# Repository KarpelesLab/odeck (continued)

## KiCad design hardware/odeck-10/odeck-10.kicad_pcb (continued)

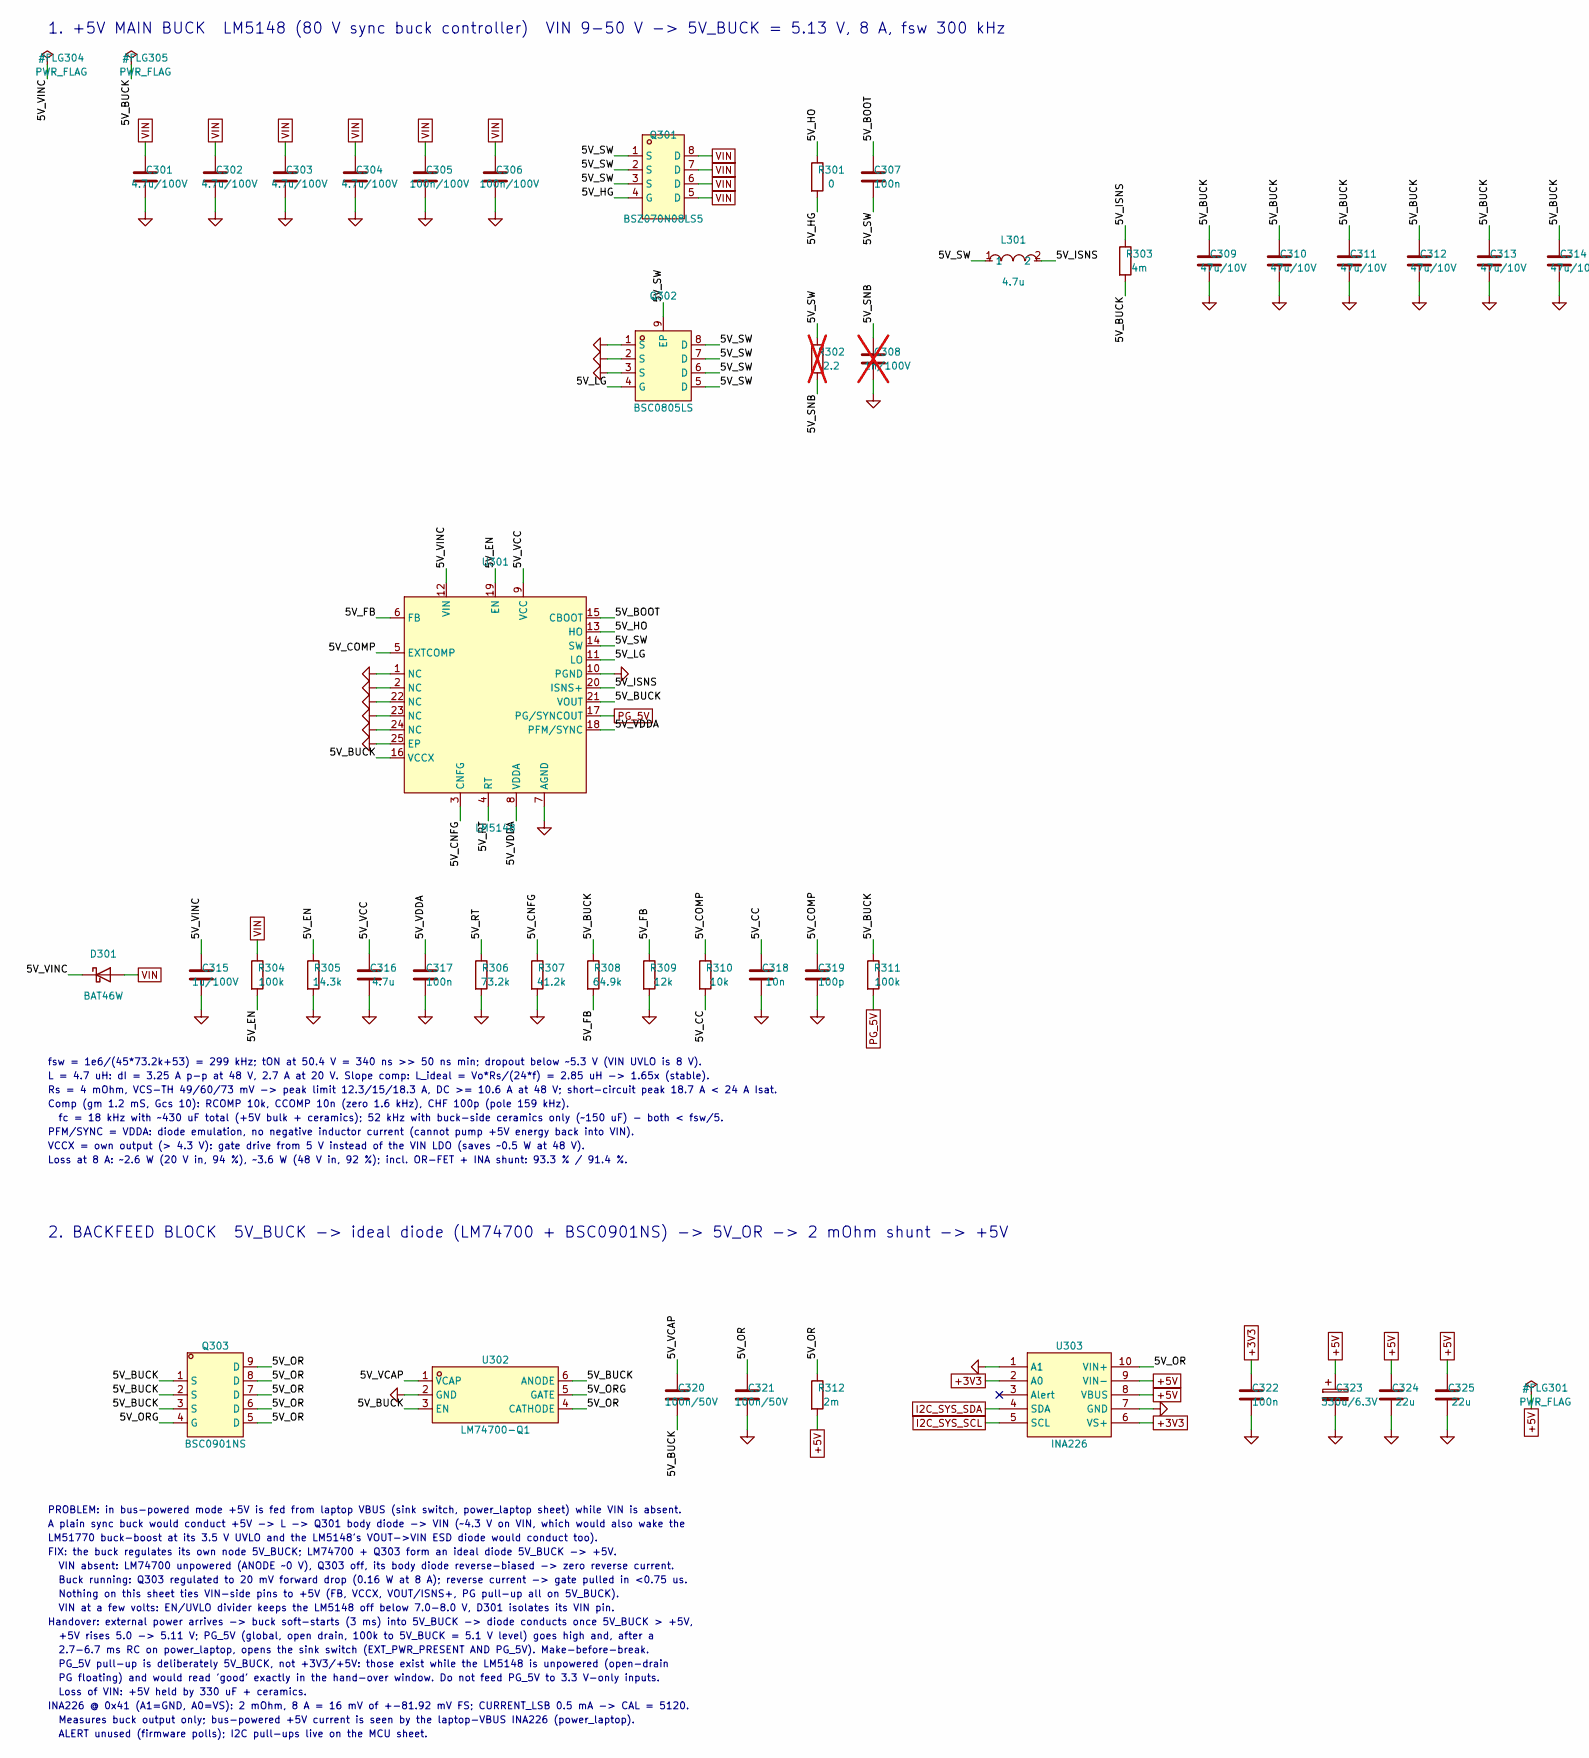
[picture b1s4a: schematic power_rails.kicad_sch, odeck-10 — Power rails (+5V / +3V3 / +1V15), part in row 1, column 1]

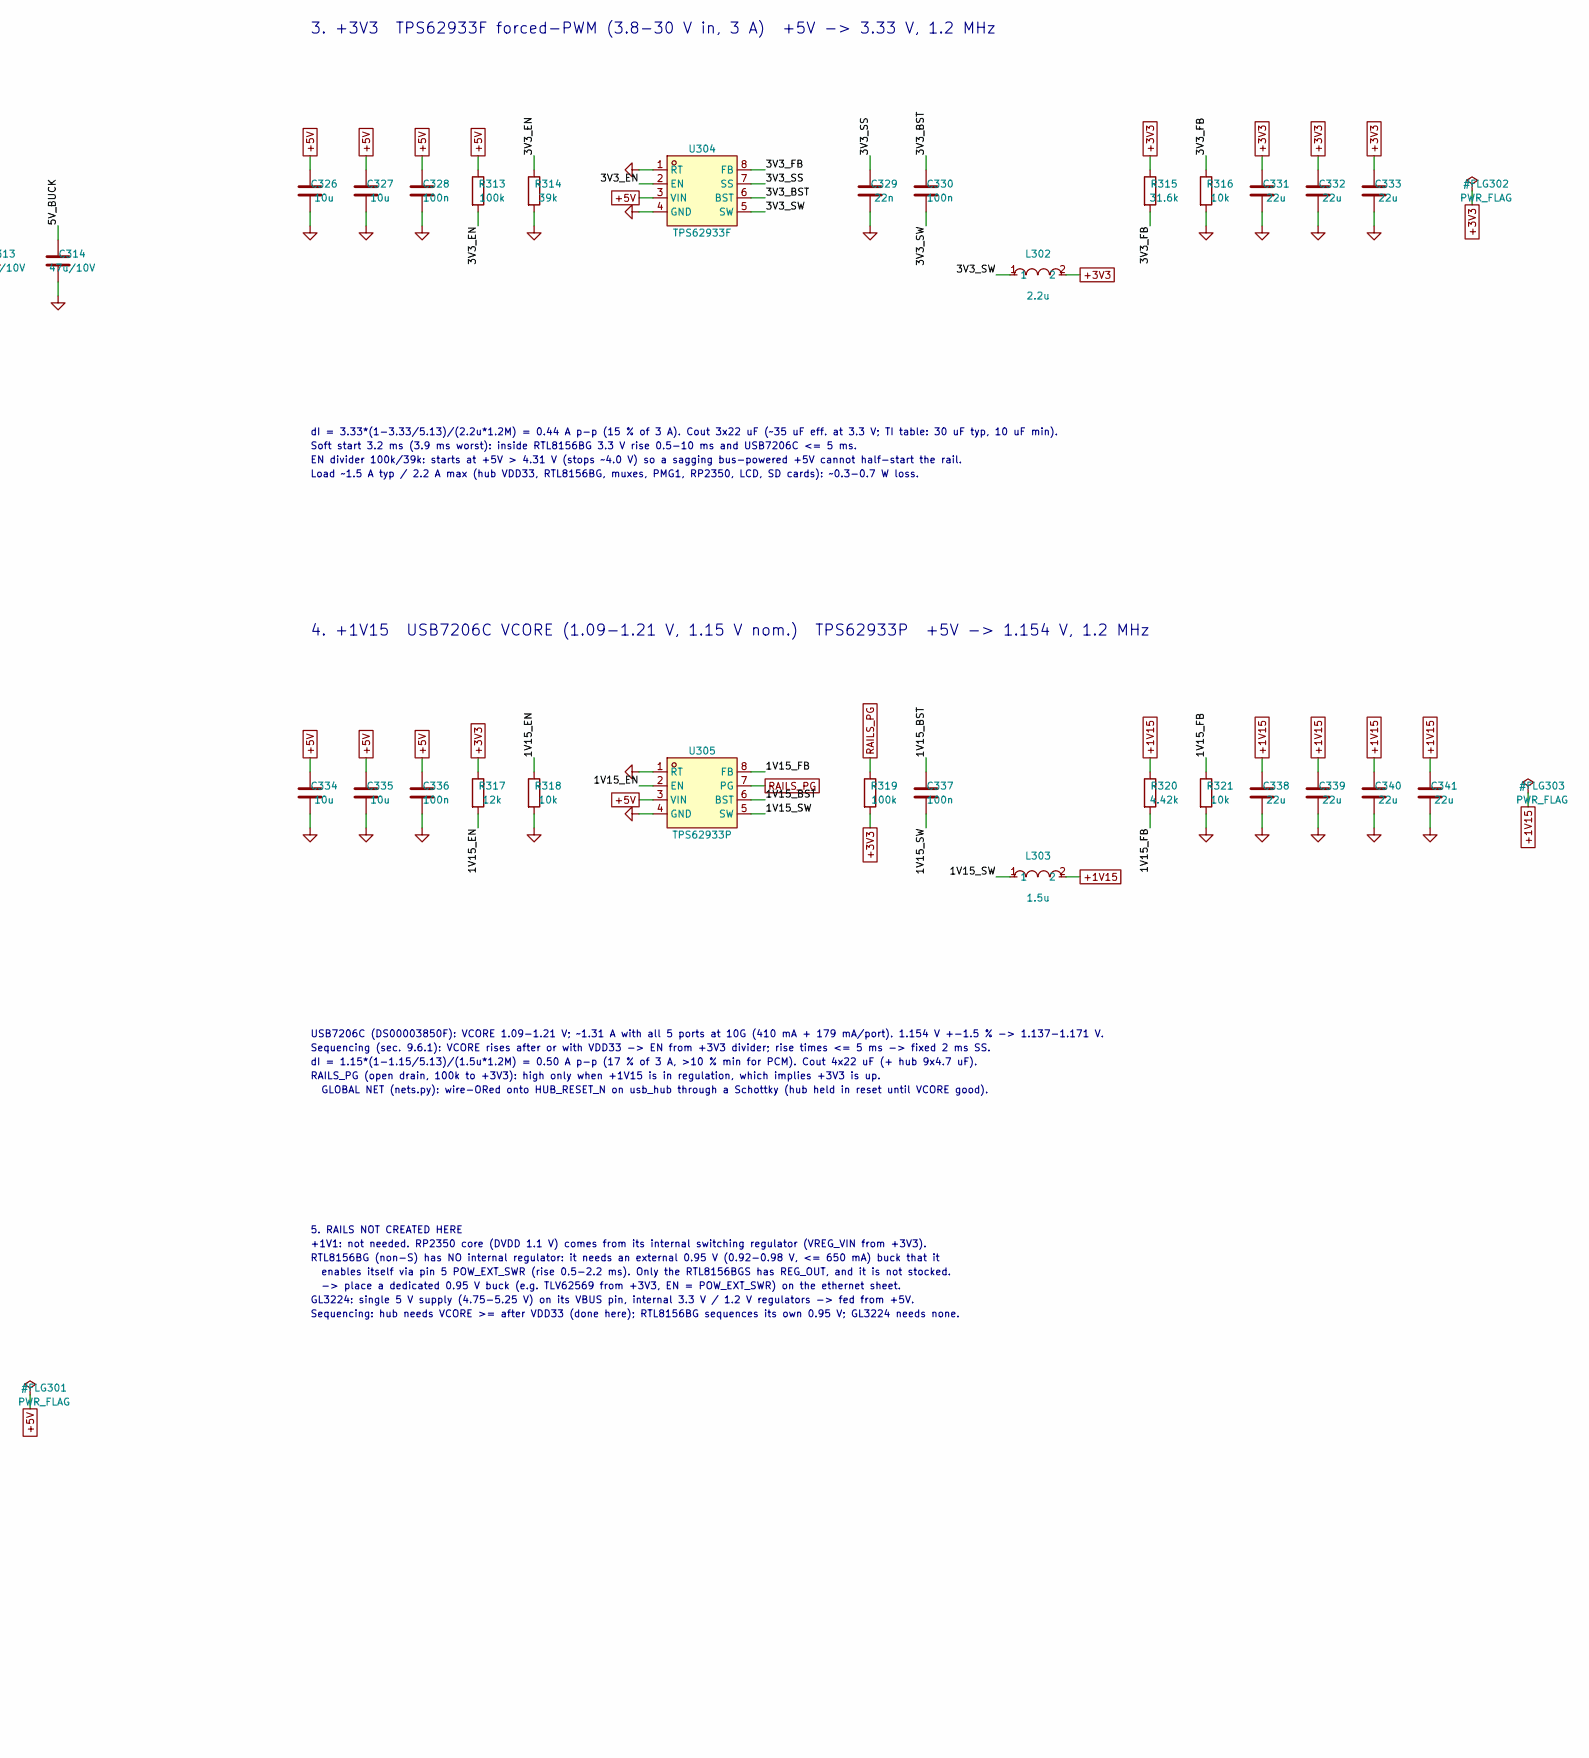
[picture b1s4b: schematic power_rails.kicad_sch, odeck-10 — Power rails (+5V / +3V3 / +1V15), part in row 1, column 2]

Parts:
C301, C302, C303, C304: 4.7u/100V; C_1210_3225Metric; LCSC C697607
C305, C306: 100n/100V; C_0805_2012Metric; LCSC C28233
C307, C317, C322, C328, C330, C336, C337: 100n; C_0402_1005Metric; LCSC C1525
C308: 1n/100V; C_0603_1608Metric; LCSC C106247; not fitted
C309, C310, C311, C312, C313, C314: 47u/10V; C_1210_3225Metric; LCSC C84494
C315: 1u/100V; C_0805_2012Metric; LCSC C126585
C316: 4.7u; C_0603_1608Metric; LCSC C19666
C318: 10n; C_0402_1005Metric; LCSC C15195
C319: 100p; C_0402_1005Metric; LCSC C1546
C320, C321: 100n/50V; C_0603_1608Metric; LCSC C14663
C323: 330u/6.3V; CP_Elec_6.3x5.9; LCSC C54321566
C324, C325, C331, C332, C333: 22u; C_0805_2012Metric; LCSC C45783
C326, C327, C334, C335: 10u; C_0805_2012Metric; LCSC C15850
C329: 22n; C_0402_1005Metric; LCSC C1532
C338, C339, C340, C341: 22u; C_0603_1608Metric; LCSC C59461
D301: BAT46W; D_SOD-123; LCSC C83152
L301: 4.7u; IND-SMD_L13.45-W12.6; MPN MWSA1206S-4R7MT; LCSC C408521
L302: 2.2u; IND-SMD_L5.4-W5.2; MPN MWSA0503S-2R2MT; LCSC C408408
L303: 1.5u; IND-SMD_L5.4-W5.2; MPN MWSA0503S-1R5MT; LCSC C408407
Q301: BSZ070N08LS5; PG-TSDSON-8_L3.3-W3.3-P0.65-BL-1; MPN BSZ070N08LS5; LCSC C534678
Q302: BSC0805LS; PG-TDSON-8_L5.2-W5.9-P1.27-LS6.2-BL-EP; MPN BSC0805LS; LCSC C534374
Q303: BSC0901NS; DFN-8_L5.9-W5.2-P1.27-LS6.2-BL; MPN BSC0901NS; LCSC C152424
R301: 0; R_0402_1005Metric; LCSC C17168
R302: 2.2; R_0805_2012Metric; LCSC C17521; not fitted
R303: 4m; R_2512_6332Metric; LCSC C459681
R304: 100k; R_0805_2012Metric; LCSC C149504
R305: 14.3k; R_0402_1005Metric; LCSC C25855
R306: 73.2k; R_0402_1005Metric; LCSC C26986
R307: 41.2k; R_0402_1005Metric; LCSC C100420
R308: 64.9k; R_0402_1005Metric; LCSC C26984
R309, R317: 12k; R_0402_1005Metric; LCSC C25752
R310, R316, R318, R321: 10k; R_0402_1005Metric; LCSC C25744
R311, R313, R319: 100k; R_0402_1005Metric; LCSC C25741
R312: 2m; R_2512_6332Metric; LCSC C459679
R314: 39k; R_0603_1608Metric; LCSC C23153
R315: 31.6k; R_0402_1005Metric; LCSC C11463
R320: 4.42k; R_0402_1005Metric; LCSC C52269
U301: LM5148; VQFN-24_L5.5-W3.5-P0.50-BL-EP-2; MPN LM5148RGYR; LCSC C7470701
U302: LM74700-Q1; SOT-23-6_L2.9-W1.6-P0.95-LS2.8-TL; MPN LM74700QDBVTQ1; LCSC C2653623
U303: INA226; MSOP-10_L3.0-W3.0-P0.50-LS5.0-BL; MPN INA226AIDGSR; LCSC C49851
U304: TPS62933F; SOT-583-8_L2.1-W1.2-P0.50-LS1.6-BR; MPN TPS62933FDRLR; LCSC C5219272
U305: TPS62933P; SOT-583-8_L2.1-W1.2-P0.50-LS1.6-BL; MPN TPS62933PDRLR; LCSC C5219254

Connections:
+1V15: C338.1, C339.1, C340.1, C341.1, L303.2, R320.1; also elsewhere on the board
+3V3: C322.1, C331.1, C332.1, C333.1, L302.2, R315.1, R317.1, R319.2, U303.2 (A0), U303.6 (VS+); also elsewhere on the board
+5V: C323.1, C324.1, C325.1, C326.1, C327.1, C328.1, C334.1, C335.1, C336.1, R312.2, R313.1, U303.8 (VBUS), U303.9 (VIN-), U304.3 (VIN), U305.3 (VIN); also elsewhere on the board
/Rails/1V15_BST: C337.1, U305.6 (BST)
/Rails/1V15_EN: R317.2, R318.1, U305.2 (EN)
/Rails/1V15_FB: R320.2, R321.1, U305.8 (FB)
/Rails/1V15_SW: C337.2, L303.1, U305.5 (SW)
/Rails/3V3_BST: C330.1, U304.6 (BST)
/Rails/3V3_EN: R313.2, R314.1, U304.2 (EN)
/Rails/3V3_FB: R315.2, R316.1, U304.8 (FB)
/Rails/3V3_SS: C329.1, U304.7 (SS)
/Rails/3V3_SW: C330.2, L302.1, U304.5 (SW)
/Rails/5V_BOOT: C307.1, U301.15 (CBOOT)
/Rails/5V_BUCK: C309.1, C310.1, C311.1, C312.1, C313.1, C314.1, C320.2, Q303.1 (S), Q303.2 (S), Q303.3 (S), R303.2, R308.1, R311.1, U301.16 (VCCX), U301.21 (VOUT), U302.3 (EN), U302.6 (ANODE)
/Rails/5V_CC: C318.1, R310.2
/Rails/5V_CNFG: R307.1, U301.3 (CNFG)
/Rails/5V_COMP: C319.1, R310.1, U301.5 (EXTCOMP)
/Rails/5V_EN: R304.2, R305.1, U301.19 (EN)
/Rails/5V_FB: R308.2, R309.1, U301.6 (FB)
/Rails/5V_HG: Q301.4 (G), R301.2
/Rails/5V_HO: R301.1, U301.13 (HO)
/Rails/5V_ISNS: L301.2, R303.1, U301.20 (ISNS+)
/Rails/5V_LG: Q302.4 (G), U301.11 (LO)
/Rails/5V_OR: C321.1, Q303.5 (D), Q303.6 (D), Q303.7 (D), Q303.8 (D), Q303.9 (D), R312.1, U302.4 (CATHODE), U303.10 (VIN+)
/Rails/5V_ORG: Q303.4 (G), U302.5 (GATE)
/Rails/5V_RT: R306.1, U301.4 (RT)
/Rails/5V_SNB: C308.1, R302.2
/Rails/5V_SW: C307.2, L301.1, Q301.1 (S), Q301.2 (S), Q301.3 (S), Q302.5 (D), Q302.6 (D), Q302.7 (D), Q302.8 (D), Q302.9 (EP), R302.1, U301.14 (SW)
/Rails/5V_VCAP: C320.1, U302.1 (VCAP)
/Rails/5V_VCC: C316.1, U301.9 (VCC)
/Rails/5V_VDDA: C317.1, U301.8 (VDDA), U301.18 (PFM/SYNC)
/Rails/5V_VINC: C315.1, D301.1 (K), U301.12 (VIN)
GND: C301.2, C302.2, C303.2, C304.2, C305.2, C306.2, C308.2, C309.2, C310.2, C311.2, C312.2, C313.2, C314.2, C315.2, C316.2, C317.2, C318.2, C319.2, C321.2, C322.2, C323.2, C324.2, C325.2, C326.2, C327.2, C328.2, C329.2, C331.2, C332.2, C333.2, C334.2, C335.2, C336.2, C338.2, C339.2, C340.2, C341.2, Q302.1 (S), Q302.2 (S), Q302.3 (S), R305.2, R306.2, R307.2, R309.2, R314.2, R316.2, R318.2, R321.2, U301.1 (NC), U301.2 (NC), U301.7 (AGND), U301.10 (PGND), U301.22 (NC), U301.23 (NC), U301.24 (NC), U301.25 (EP), U302.2 (GND), U303.1 (A1), U303.7 (GND), U304.1 (RT), U304.4 (GND), U305.1 (RT), U305.4 (GND); also elsewhere on the board
I2C_SYS_SCL: U303.5 (SCL); also elsewhere on the board
I2C_SYS_SDA: U303.4 (SDA); also elsewhere on the board
PG_5V: R311.2, U301.17 (PG/SYNCOUT); also elsewhere on the board
RAILS_PG: R319.1, U305.7 (PG); also elsewhere on the board
VIN: C301.1, C302.1, C303.1, C304.1, C305.1, C306.1, D301.2 (A), Q301.5 (D), Q301.6 (D), Q301.7 (D), Q301.8 (D), R304.1; also elsewhere on the board

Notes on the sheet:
1. +5V MAIN BUCK LM5148 (80 V sync buck controller) VIN 9-50 V -> 5V_BUCK = 5.13 V, 8 A, fsw 300 kHz
fsw = 1e6/(45*73.2k+53) = 299 kHz; tON at 50.4 V = 340 ns >> 50 ns min; dropout below ~5.3 V (VIN UVLO is 8 V).
L = 4.7 uH: dI = 3.25 A p-p at 48 V, 2.7 A at 20 V. Slope comp: L_ideal = Vo*Rs/(24*f) = 2.85 uH -> 1.65x (stable).
Rs = 4 mOhm, VCS-TH 49/60/73 mV -> peak limit 12.3/15/18.3 A, DC >= 10.6 A at 48 V; short-circuit peak 18.7 A < 24 A Isat.
Comp (gm 1.2 mS, Gcs 10): RCOMP 10k, CCOMP 10n (zero 1.6 kHz), CHF 100p (pole 159 kHz).
fc = 18 kHz with ~430 uF total (+5V bulk + ceramics); 52 kHz with buck-side ceramics only (~150 uF) - both < fsw/5.
PFM/SYNC = VDDA: diode emulation, no negative inductor current (cannot pump +5V energy back into VIN).
VCCX = own output (> 4.3 V): gate drive from 5 V instead of the VIN LDO (saves ~0.5 W at 48 V).
Loss at 8 A: ~2.6 W (20 V in, 94 %), ~3.6 W (48 V in, 92 %); incl. OR-FET + INA shunt: 93.3 % / 91.4 %.
2. BACKFEED BLOCK 5V_BUCK -> ideal diode (LM74700 + BSC0901NS) -> 5V_OR -> 2 mOhm shunt -> +5V
PROBLEM: in bus-powered mode +5V is fed from laptop VBUS (sink switch, power_laptop sheet) while VIN is absent.
A plain sync buck would conduct +5V -> L -> Q301 body diode -> VIN (~4.3 V on VIN, which would also wake the
LM51770 buck-boost at its 3.5 V UVLO and the LM5148's VOUT->VIN ESD diode would conduct too).
FIX: the buck regulates its own node 5V_BUCK; LM74700 + Q303 form an ideal diode 5V_BUCK -> +5V.
VIN absent: LM74700 unpowered (ANODE ~0 V), Q303 off, its body diode reverse-biased -> zero reverse current.
Buck running: Q303 regulated to 20 mV forward drop (0.16 W at 8 A); reverse current -> gate pulled in <0.75 us.
Nothing on this sheet ties VIN-side pins to +5V (FB, VCCX, VOUT/ISNS+, PG pull-up all on 5V_BUCK).
VIN at a few volts: EN/UVLO divider keeps the LM5148 off below 7.0-8.0 V, D301 isolates its VIN pin.
Handover: external power arrives -> buck soft-starts (3 ms) into 5V_BUCK -> diode conducts once 5V_BUCK > +5V,
+5V rises 5.0 -> 5.11 V; PG_5V (global, open drain, 100k to 5V_BUCK = 5.1 V level) goes high and, after a
2.7-6.7 ms RC on power_laptop, opens the sink switch (EXT_PWR_PRESENT AND PG_5V). Make-before-break.
PG_5V pull-up is deliberately 5V_BUCK, not +3V3/+5V: those exist while the LM5148 is unpowered (open-drain
PG floating) and would read 'good' exactly in the hand-over window. Do not feed PG_5V to 3.3 V-only inputs.
Loss of VIN: +5V held by 330 uF + ceramics.
INA226 @ 0x41 (A1=GND, A0=VS): 2 mOhm, 8 A = 16 mV of +-81.92 mV FS; CURRENT_LSB 0.5 mA -> CAL = 5120.
Measures buck output only; bus-powered +5V current is seen by the laptop-VBUS INA226 (power_laptop).
ALERT unused (firmware polls); I2C pull-ups live on the MCU sheet.
3. +3V3 TPS62933F forced-PWM (3.8-30 V in, 3 A) +5V -> 3.33 V, 1.2 MHz
dI = 3.33*(1-3.33/5.13)/(2.2u*1.2M) = 0.44 A p-p (15 % of 3 A). Cout 3x22 uF (~35 uF eff. at 3.3 V; TI table: 30 uF typ, 10 uF min).
Soft start 3.2 ms (3.9 ms worst): inside RTL8156BG 3.3 V rise 0.5-10 ms and USB7206C <= 5 ms.
EN divider 100k/39k: starts at +5V > 4.31 V (stops ~4.0 V) so a sagging bus-powered +5V cannot half-start the rail.
Load ~1.5 A typ / 2.2 A max (hub VDD33, RTL8156BG, muxes, PMG1, RP2350, LCD, SD cards): ~0.3-0.7 W loss.
4. +1V15 USB7206C VCORE (1.09-1.21 V, 1.15 V nom.) TPS62933P +5V -> 1.154 V, 1.2 MHz
USB7206C (DS00003850F): VCORE 1.09-1.21 V; ~1.31 A with all 5 ports at 10G (410 mA + 179 mA/port). 1.154 V +-1.5 % -> 1.137-1.171 V.
Sequencing (sec. 9.6.1): VCORE rises after or with VDD33 -> EN from +3V3 divider; rise times <= 5 ms -> fixed 2 ms SS.
dI = 1.15*(1-1.15/5.13)/(1.5u*1.2M) = 0.50 A p-p (17 % of 3 A, >10 % min for PCM). Cout 4x22 uF (+ hub 9x4.7 uF).
RAILS_PG (open drain, 100k to +3V3): high only when +1V15 is in regulation, which implies +3V3 is up.
GLOBAL NET (nets.py): wire-ORed onto HUB_RESET_N on usb_hub through a Schottky (hub held in reset until VCORE good).
5. RAILS NOT CREATED HERE
+1V1: not needed. RP2350 core (DVDD 1.1 V) comes from its internal switching regulator (VREG_VIN from +3V3).

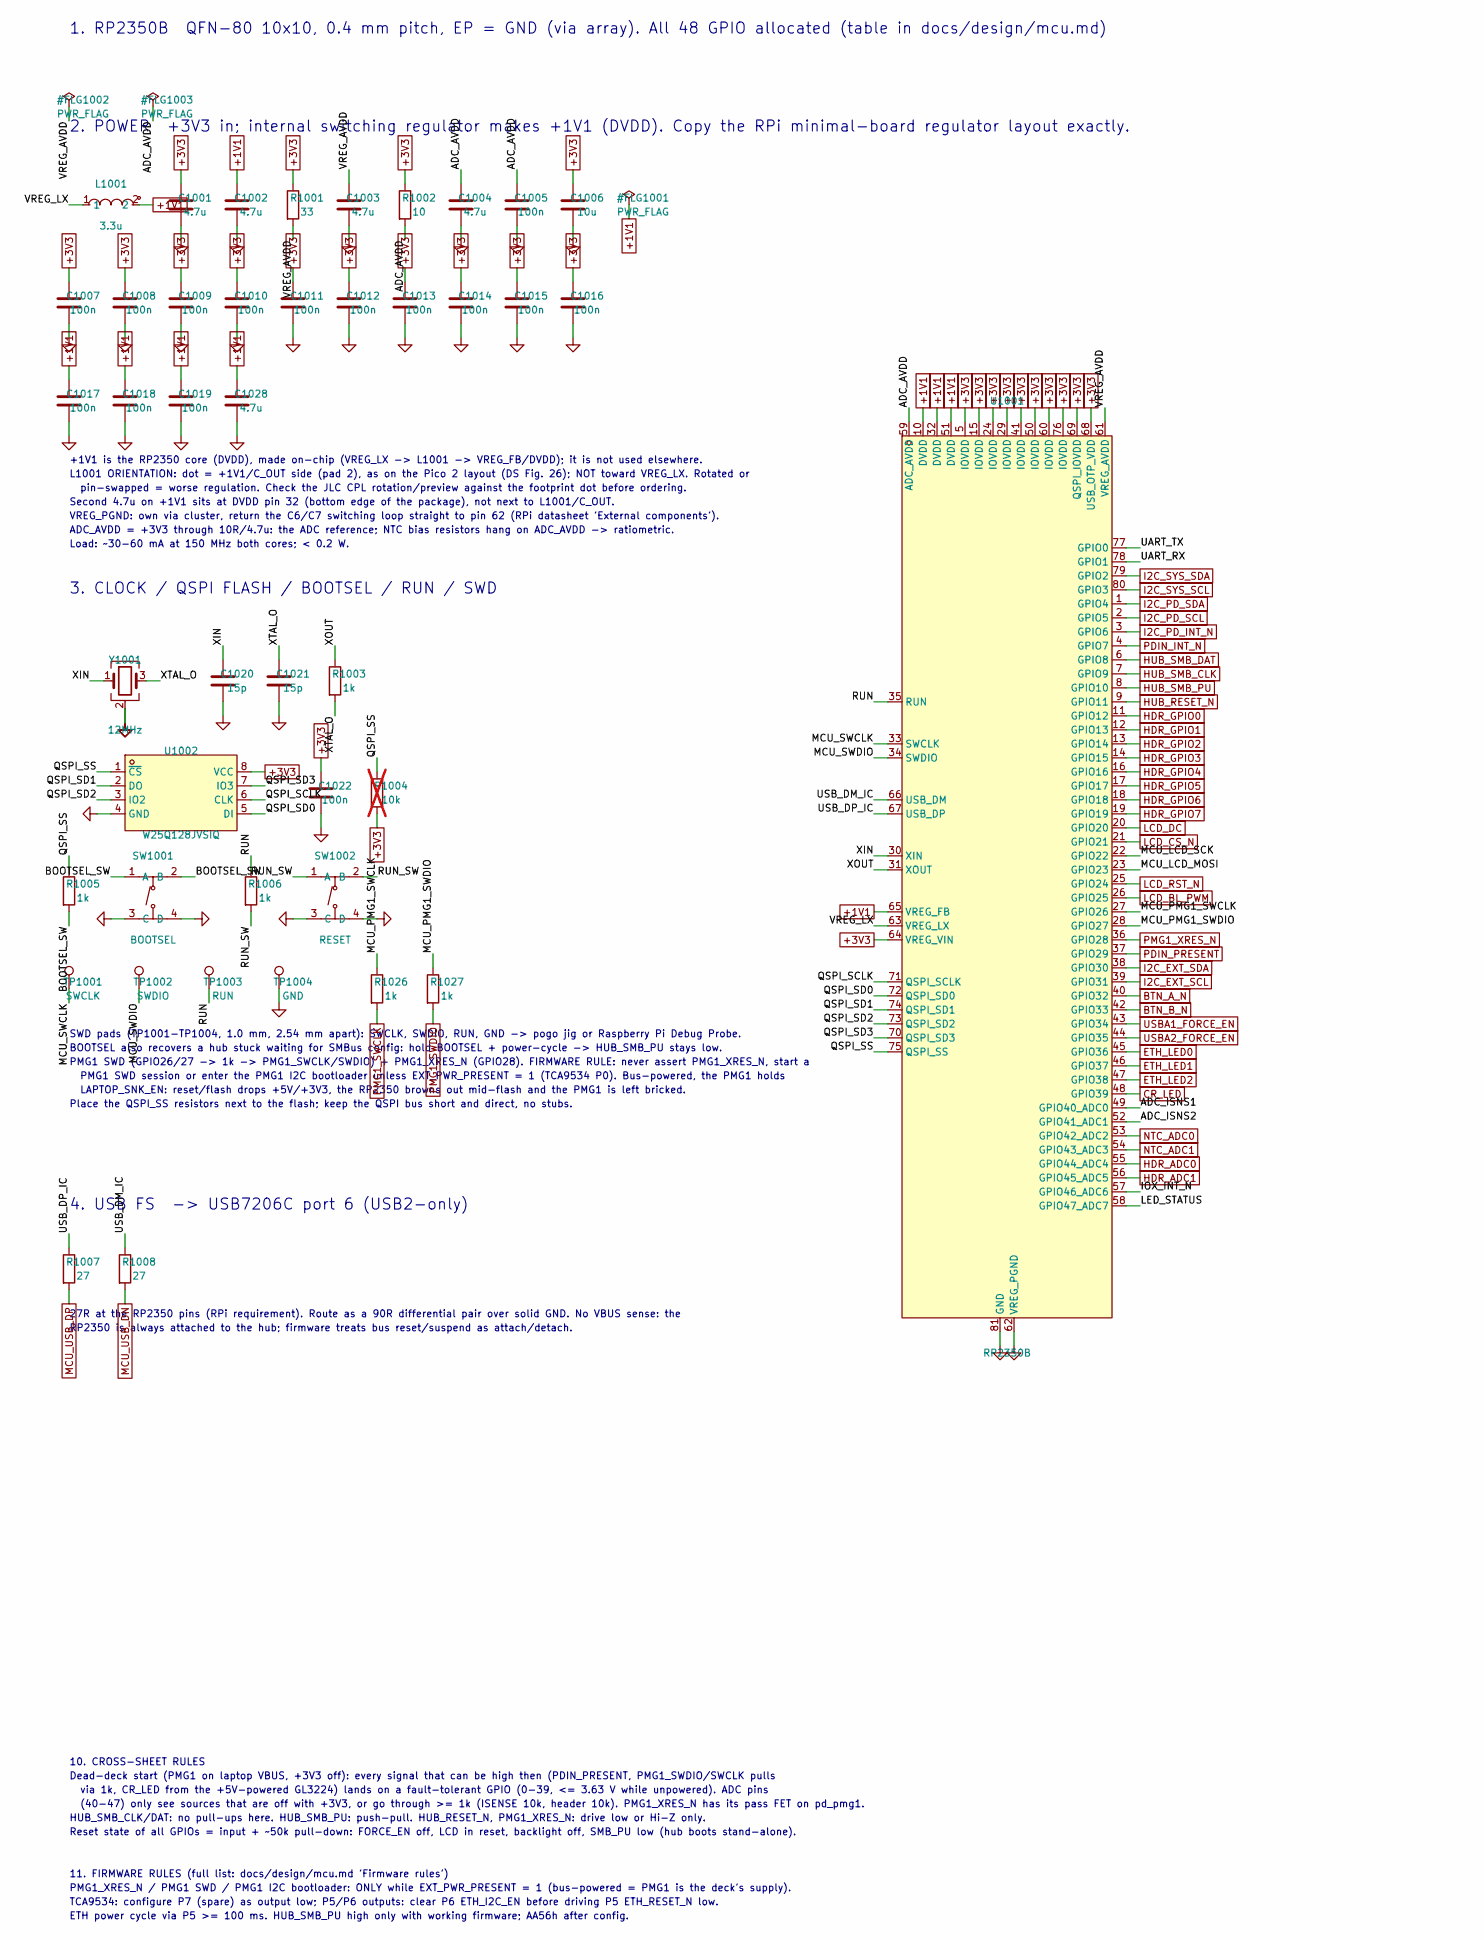
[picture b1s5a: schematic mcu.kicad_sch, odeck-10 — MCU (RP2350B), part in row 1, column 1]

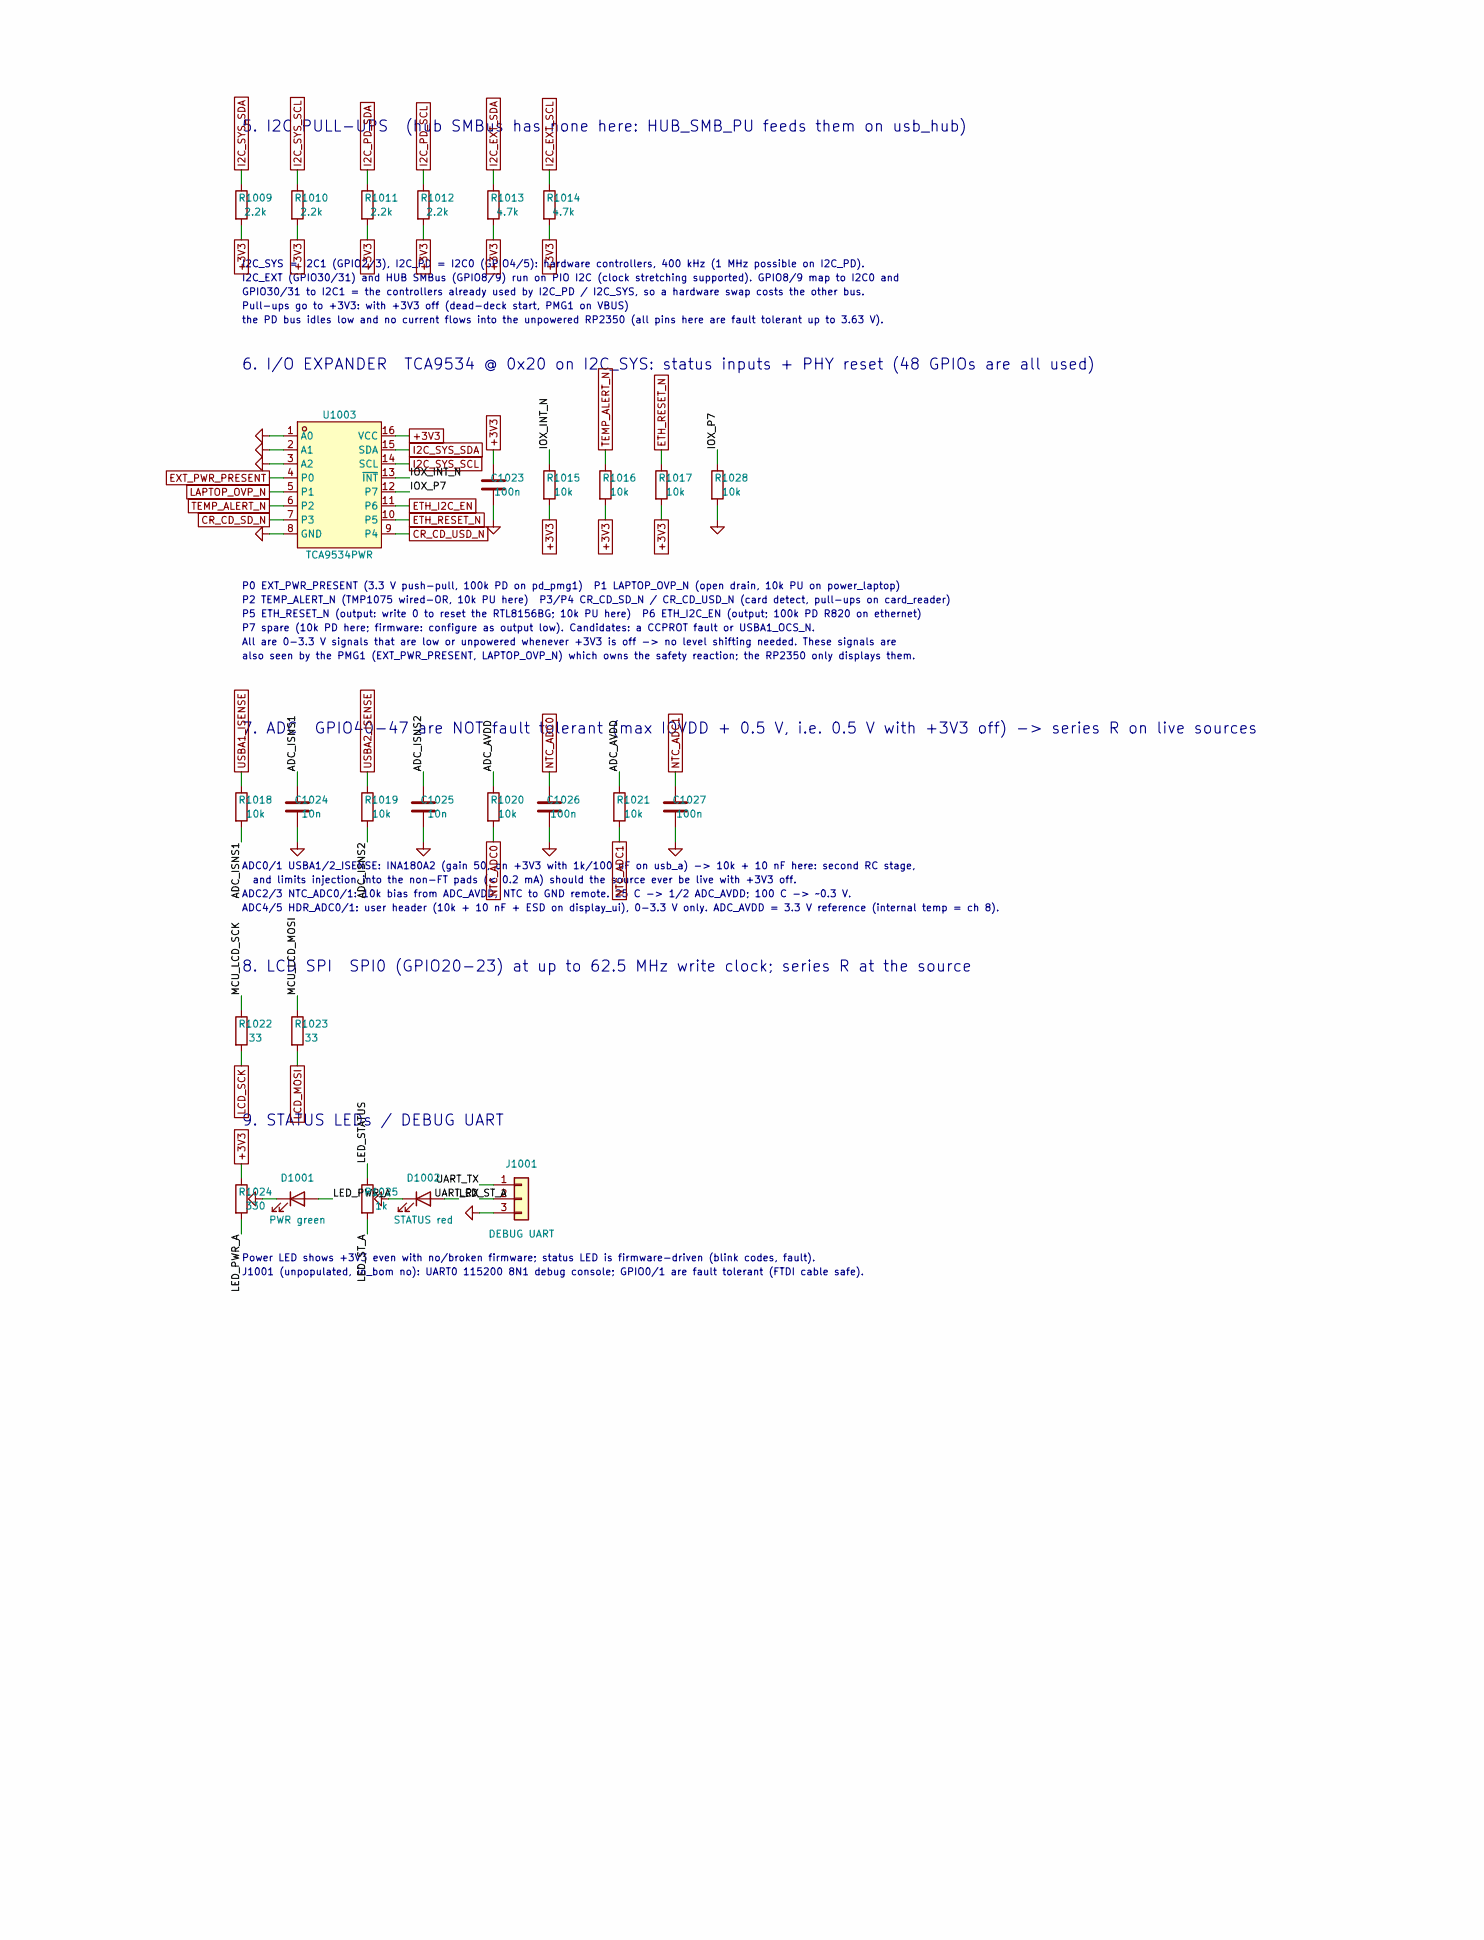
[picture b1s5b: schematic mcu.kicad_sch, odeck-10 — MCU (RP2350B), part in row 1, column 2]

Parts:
C1001, C1002, C1003, C1004, C1028: 4.7u; C_0402_1005Metric; LCSC C23733
C1005, C1007, C1008, C1009, C1010, C1011, C1012, C1013, C1014, C1015, C1016, C1017, C1018, C1019, C1022, C1023, C1026, C1027: 100n; C_0402_1005Metric; LCSC C1525
C1006: 10u; C_0603_1608Metric; LCSC C19702
C1020, C1021: 15p; C_0402_1005Metric; LCSC C1548
C1024, C1025: 10n; C_0402_1005Metric; LCSC C15195
D1001: PWR green; LED_0805_2012Metric; LCSC C2297
D1002: STATUS red; LED_0603_1608Metric; LCSC C2286
J1001: DEBUG UART; PinHeader_1x03_P2.54mm_Vertical
L1001: 3.3u; IND-SMD_L2.0-W1.6_AOTA-B201610S3R3-101-T; MPN AOTA-B201610S3R3-101-T; LCSC C42411119
R1001, R1022, R1023: 33; R_0402_1005Metric; LCSC C25105
R1002: 10; R_0402_1005Metric; LCSC C25077
R1003, R1005, R1006, R1025, R1026, R1027: 1k; R_0402_1005Metric; LCSC C11702
R1004: 10k; R_0402_1005Metric; LCSC C25744; not fitted
R1007, R1008: 27; R_0402_1005Metric; LCSC C25100
R1009, R1010, R1011, R1012: 2.2k; R_0402_1005Metric; LCSC C25879
R1013, R1014: 4.7k; R_0402_1005Metric; LCSC C25900
R1015, R1016, R1017, R1018, R1019, R1020, R1021, R1028: 10k; R_0402_1005Metric; LCSC C25744
R1024: 330; R_0402_1005Metric; LCSC C25104
SW1001: BOOTSEL; SW-SMD_4P-L5.1-W5.1-P3.70-LS6.5-TL_H1.5; MPN TS-1187A-B-A-B; LCSC C318884
SW1002: RESET; SW-SMD_4P-L5.1-W5.1-P3.70-LS6.5-TL_H1.5; MPN TS-1187A-B-A-B; LCSC C318884
TP1001: SWCLK; TestPoint_Pad_D1.0mm
TP1002: SWDIO; TestPoint_Pad_D1.0mm
TP1003: RUN; TestPoint_Pad_D1.0mm
TP1004: GND; TestPoint_Pad_D1.0mm
U1001: RP2350B; QFN-80_L10.0-W10.0-P0.40-TL-EP3.4; MPN RP2350B; LCSC C42415655
U1002: W25Q128JVSIQ; SOIC-8_L5.3-W5.3-P1.27-LS8.0-BL; MPN W25Q128JVSIQ; LCSC C97521
U1003: TCA9534PWR; TSSOP-16_L5.0-W4.4-P0.65-LS6.4-BL; MPN TCA9534PWR; LCSC C783615
Y1001: 12MHz; Crystal_SMD_3225-4Pin_3.2x2.5mm; LCSC C20625731

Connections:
+1V1: C1002.1, C1017.1, C1018.1, C1019.1, C1028.1, L1001.2, U1001.10 (DVDD), U1001.32 (DVDD), U1001.51 (DVDD), U1001.65 (VREG_FB)
+3V3: C1001.1, C1006.1, C1007.1, C1008.1, C1009.1, C1010.1, C1011.1, C1012.1, C1013.1, C1014.1, C1015.1, C1016.1, C1022.1, C1023.1, R1001.1, R1002.1, R1004.2, R1009.2, R1010.2, R1011.2, R1012.2, R1013.2, R1014.2, R1015.2, R1016.2, R1017.2, R1024.1, U1001.5 (IOVDD), U1001.15 (IOVDD), U1001.24 (IOVDD), U1001.29 (IOVDD), U1001.41 (IOVDD), U1001.50 (IOVDD), U1001.60 (IOVDD), U1001.64 (VREG_VIN), U1001.68 (USB_OTP_VDD), U1001.69 (QSPI_IOVDD), U1001.76 (IOVDD), U1002.8 (VCC), U1003.16 (VCC); also elsewhere on the board
/MCU/ADC_AVDD: C1004.1, C1005.1, R1002.2, R1020.1, R1021.1, U1001.59 (ADC_AVDD)
/MCU/ADC_ISNS1: C1024.1, R1018.2, U1001.49 (GPIO40_ADC0)
/MCU/ADC_ISNS2: C1025.1, R1019.2, U1001.52 (GPIO41_ADC1)
/MCU/BOOTSEL_SW: R1005.2, SW1001.1 (A), SW1001.2 (B)
/MCU/IOX_INT_N: R1015.1, U1001.57 (GPIO46_ADC6), U1003.13 (~INT)
/MCU/IOX_P7: R1028.1, U1003.12 (P7)
/MCU/LED_PWR_A: D1001.2 (A), R1024.2
/MCU/LED_STATUS: R1025.1, U1001.58 (GPIO47_ADC7)
/MCU/LED_ST_A: D1002.2 (A), R1025.2
/MCU/MCU_LCD_MOSI: R1023.1, U1001.23 (GPIO23)
/MCU/MCU_LCD_SCK: R1022.1, U1001.22 (GPIO22)
/MCU/MCU_PMG1_SWCLK: R1026.1, U1001.27 (GPIO26)
/MCU/MCU_PMG1_SWDIO: R1027.1, U1001.28 (GPIO27)
/MCU/MCU_SWCLK: TP1001.1, U1001.33 (SWCLK)
/MCU/MCU_SWDIO: TP1002.1, U1001.34 (SWDIO)
/MCU/QSPI_SCLK: U1001.71 (QSPI_SCLK), U1002.6 (CLK)
/MCU/QSPI_SD0: U1001.72 (QSPI_SD0), U1002.5 (DI)
/MCU/QSPI_SD1: U1001.74 (QSPI_SD1), U1002.2 (DO)
/MCU/QSPI_SD2: U1001.73 (QSPI_SD2), U1002.3 (IO2)
/MCU/QSPI_SD3: U1001.70 (QSPI_SD3), U1002.7 (IO3)
/MCU/QSPI_SS: R1004.1, R1005.1, U1001.75 (QSPI_SS), U1002.1 (~CS)
/MCU/RUN: R1006.1, TP1003.1, U1001.35 (RUN)
/MCU/RUN_SW: R1006.2, SW1002.1 (A), SW1002.2 (B)
/MCU/UART_RX: J1001.2, U1001.78 (GPIO1)
/MCU/UART_TX: J1001.1, U1001.77 (GPIO0)
/MCU/USB_DM_IC: R1008.1, U1001.66 (USB_DM)
/MCU/USB_DP_IC: R1007.1, U1001.67 (USB_DP)
/MCU/VREG_AVDD: C1003.1, R1001.2, U1001.61 (VREG_AVDD)
/MCU/VREG_LX: L1001.1, U1001.63 (VREG_LX)
/MCU/XIN: C1020.1, U1001.30 (XIN), Y1001.1
/MCU/XOUT: R1003.1, U1001.31 (XOUT)
/MCU/XTAL_O: C1021.1, R1003.2, Y1001.3
BTN_A_N: U1001.40 (GPIO32); also elsewhere on the board
BTN_B_N: U1001.42 (GPIO33); also elsewhere on the board
CR_CD_SD_N: U1003.7 (P3); also elsewhere on the board
CR_CD_USD_N: U1003.9 (P4); also elsewhere on the board
CR_LED: U1001.48 (GPIO39); also elsewhere on the board
ETH_I2C_EN: U1003.11 (P6); also elsewhere on the board
ETH_LED0: U1001.45 (GPIO36); also elsewhere on the board
ETH_LED1: U1001.46 (GPIO37); also elsewhere on the board
ETH_LED2: U1001.47 (GPIO38); also elsewhere on the board
ETH_RESET_N: R1017.1, U1003.10 (P5); also elsewhere on the board
EXT_PWR_PRESENT: U1003.4 (P0); also elsewhere on the board
GND: C1001.2, C1002.2, C1003.2, C1004.2, C1005.2, C1006.2, C1007.2, C1008.2, C1009.2, C1010.2, C1011.2, C1012.2, C1013.2, C1014.2, C1015.2, C1016.2, C1017.2, C1018.2, C1019.2, C1020.2, C1021.2, C1022.2, C1023.2, C1024.2, C1025.2, C1026.2, C1027.2, C1028.2, D1001.1 (K), D1002.1 (K), J1001.3, R1028.2, SW1001.3 (C), SW1001.4 (D), SW1002.3 (C), SW1002.4 (D), TP1004.1, U1001.62 (VREG_PGND), U1001.81 (GND), U1002.4 (GND), U1003.1 (A0), U1003.2 (A1), U1003.3 (A2), U1003.8 (GND), Y1001.2 (G), Y1001.4 (G); also elsewhere on the board
HDR_ADC0: U1001.55 (GPIO44_ADC4); also elsewhere on the board
HDR_ADC1: U1001.56 (GPIO45_ADC5); also elsewhere on the board
HDR_GPIO0: U1001.11 (GPIO12); also elsewhere on the board
HDR_GPIO1: U1001.12 (GPIO13); also elsewhere on the board
HDR_GPIO2: U1001.13 (GPIO14); also elsewhere on the board
HDR_GPIO3: U1001.14 (GPIO15); also elsewhere on the board
HDR_GPIO4: U1001.16 (GPIO16); also elsewhere on the board
HDR_GPIO5: U1001.17 (GPIO17); also elsewhere on the board
HDR_GPIO6: U1001.18 (GPIO18); also elsewhere on the board
HDR_GPIO7: U1001.19 (GPIO19); also elsewhere on the board
HUB_RESET_N: U1001.9 (GPIO11); also elsewhere on the board
HUB_SMB_CLK: U1001.7 (GPIO9); also elsewhere on the board
HUB_SMB_DAT: U1001.6 (GPIO8); also elsewhere on the board
HUB_SMB_PU: U1001.8 (GPIO10); also elsewhere on the board
I2C_EXT_SCL: R1014.1, U1001.39 (GPIO31); also elsewhere on the board
I2C_EXT_SDA: R1013.1, U1001.38 (GPIO30); also elsewhere on the board
I2C_PD_INT_N: U1001.3 (GPIO6); also elsewhere on the board
I2C_PD_SCL: R1012.1, U1001.2 (GPIO5); also elsewhere on the board
I2C_PD_SDA: R1011.1, U1001.1 (GPIO4); also elsewhere on the board
I2C_SYS_SCL: R1010.1, U1001.80 (GPIO3), U1003.14 (SCL); also elsewhere on the board
I2C_SYS_SDA: R1009.1, U1001.79 (GPIO2), U1003.15 (SDA); also elsewhere on the board
LAPTOP_OVP_N: U1003.5 (P1); also elsewhere on the board
LCD_BL_PWM: U1001.26 (GPIO25); also elsewhere on the board
LCD_CS_N: U1001.21 (GPIO21); also elsewhere on the board
LCD_DC: U1001.20 (GPIO20); also elsewhere on the board
LCD_MOSI: R1023.2; also elsewhere on the board
LCD_RST_N: U1001.25 (GPIO24); also elsewhere on the board
LCD_SCK: R1022.2; also elsewhere on the board
MCU_USB_DN: R1008.2; also elsewhere on the board
MCU_USB_DP: R1007.2; also elsewhere on the board
NTC_ADC0: C1026.1, R1020.2, U1001.53 (GPIO42_ADC2); also elsewhere on the board
NTC_ADC1: C1027.1, R1021.2, U1001.54 (GPIO43_ADC3); also elsewhere on the board
PDIN_INT_N: U1001.4 (GPIO7); also elsewhere on the board
PDIN_PRESENT: U1001.37 (GPIO29); also elsewhere on the board
PMG1_SWCLK: R1026.2; also elsewhere on the board
PMG1_SWDIO: R1027.2; also elsewhere on the board
PMG1_XRES_N: U1001.36 (GPIO28); also elsewhere on the board
TEMP_ALERT_N: R1016.1, U1003.6 (P2); also elsewhere on the board
USBA1_FORCE_EN: U1001.43 (GPIO34); also elsewhere on the board
USBA1_ISENSE: R1018.1; also elsewhere on the board
USBA2_FORCE_EN: U1001.44 (GPIO35); also elsewhere on the board
USBA2_ISENSE: R1019.1; also elsewhere on the board

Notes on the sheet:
1. RP2350B QFN-80 10x10, 0.4 mm pitch, EP = GND (via array). All 48 GPIO allocated (table in docs/design/mcu.md)
2. POWER +3V3 in; internal switching regulator makes +1V1 (DVDD). Copy the RPi minimal-board regulator layout exactly.
+1V1 is the RP2350 core (DVDD), made on-chip (VREG_LX -> L1001 -> VREG_FB/DVDD); it is not used elsewhere.
L1001 ORIENTATION: dot = +1V1/C_OUT side (pad 2), as on the Pico 2 layout (DS Fig. 26); NOT toward VREG_LX. Rotated or
pin-swapped = worse regulation. Check the JLC CPL rotation/preview against the footprint dot before ordering.
Second 4.7u on +1V1 sits at DVDD pin 32 (bottom edge of the package), not next to L1001/C_OUT.
VREG_PGND: own via cluster, return the C6/C7 switching loop straight to pin 62 (RPi datasheet 'External components').
ADC_AVDD = +3V3 through 10R/4.7u: the ADC reference; NTC bias resistors hang on ADC_AVDD -> ratiometric.
Load: ~30-60 mA at 150 MHz both cores; < 0.2 W.
3. CLOCK / QSPI FLASH / BOOTSEL / RUN / SWD
SWD pads (TP1001-TP1004, 1.0 mm, 2.54 mm apart): SWCLK, SWDIO, RUN, GND -> pogo jig or Raspberry Pi Debug Probe.
BOOTSEL also recovers a hub stuck waiting for SMBus config: hold BOOTSEL + power-cycle -> HUB_SMB_PU stays low.
PMG1 SWD (GPIO26/27 -> 1k -> PMG1_SWCLK/SWDIO) + PMG1_XRES_N (GPIO28). FIRMWARE RULE: never assert PMG1_XRES_N, start a
PMG1 SWD session or enter the PMG1 I2C bootloader unless EXT_PWR_PRESENT = 1 (TCA9534 P0). Bus-powered, the PMG1 holds
LAPTOP_SNK_EN: reset/flash drops +5V/+3V3, the RP2350 browns out mid-flash and the PMG1 is left bricked.
Place the QSPI_SS resistors next to the flash; keep the QSPI bus short and direct, no stubs.
4. USB FS -> USB7206C port 6 (USB2-only)
27R at the RP2350 pins (RPi requirement). Route as a 90R differential pair over solid GND. No VBUS sense: the
RP2350 is always attached to the hub; firmware treats bus reset/suspend as attach/detach.
5. I2C PULL-UPS (hub SMBus has none here: HUB_SMB_PU feeds them on usb_hub)
I2C_SYS = I2C1 (GPIO2/3), I2C_PD = I2C0 (GPIO4/5): hardware controllers, 400 kHz (1 MHz possible on I2C_PD).
I2C_EXT (GPIO30/31) and HUB SMBus (GPIO8/9) run on PIO I2C (clock stretching supported). GPIO8/9 map to I2C0 and
GPIO30/31 to I2C1 = the controllers already used by I2C_PD / I2C_SYS, so a hardware swap costs the other bus.
Pull-ups go to +3V3: with +3V3 off (dead-deck start, PMG1 on VBUS)
the PD bus idles low and no current flows into the unpowered RP2350 (all pins here are fault tolerant up to 3.63 V).
6. I/O EXPANDER TCA9534 @ 0x20 on I2C_SYS: status inputs + PHY reset (48 GPIOs are all used)
P0 EXT_PWR_PRESENT (3.3 V push-pull, 100k PD on pd_pmg1) P1 LAPTOP_OVP_N (open drain, 10k PU on power_laptop)
P2 TEMP_ALERT_N (TMP1075 wired-OR, 10k PU here) P3/P4 CR_CD_SD_N / CR_CD_USD_N (card detect, pull-ups on card_reader)
P5 ETH_RESET_N (output: write 0 to reset the RTL8156BG; 10k PU here) P6 ETH_I2C_EN (output; 100k PD R820 on ethernet)
P7 spare (10k PD here; firmware: configure as output low). Candidates: a CCPROT fault or USBA1_OCS_N.
All are 0-3.3 V signals that are low or unpowered whenever +3V3 is off -> no level shifting needed. These signals are
also seen by the PMG1 (EXT_PWR_PRESENT, LAPTOP_OVP_N) which owns the safety reaction; the RP2350 only displays them.
7. ADC GPIO40-47 are NOT fault tolerant (max IOVDD + 0.5 V, i.e. 0.5 V with +3V3 off) -> series R on live sources
ADC0/1 USBA1/2_ISENSE: INA180A2 (gain 50, on +3V3 with 1k/100 nF on usb_a) -> 10k + 10 nF here: second RC stage,
and limits injection into the non-FT pads (< 0.2 mA) should the source ever be live with +3V3 off.
ADC2/3 NTC_ADC0/1: 10k bias from ADC_AVDD, NTC to GND remote. 25 C -> 1/2 ADC_AVDD; 100 C -> ~0.3 V.
ADC4/5 HDR_ADC0/1: user header (10k + 10 nF + ESD on display_ui), 0-3.3 V only. ADC_AVDD = 3.3 V reference (internal temp = ch 8).
8. LCD SPI SPI0 (GPIO20-23) at up to 62.5 MHz write clock; series R at the source
9. STATUS LEDs / DEBUG UART
Power LED shows +3V3 even with no/broken firmware; status LED is firmware-driven (blink codes, fault).
